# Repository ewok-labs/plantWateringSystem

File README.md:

plantWateringSystem
===================

plant watering system for the HPI HCI Lab, based on arduino

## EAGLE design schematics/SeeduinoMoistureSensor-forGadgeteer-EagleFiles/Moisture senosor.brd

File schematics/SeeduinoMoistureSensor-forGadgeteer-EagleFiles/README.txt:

Basically this is a gadgeteer compatible module (uses this 10-pin connector).
I've made it usable under arduino, the schematics from Seeduino guys are weird because they reported SIG_IN and SIG_OUT flipped (at least in my logic).
I've simple flipped them and renamed it to SIG_IN_REAL and SIG_OUT_REAL

The sensor will act like: http://www.seeedstudio.com/wiki/Grove_-_Moisture_Sensor
After you've connected the pins to the right place :) (and send a +5v on the SIG_INPUT_REAL)

It works.

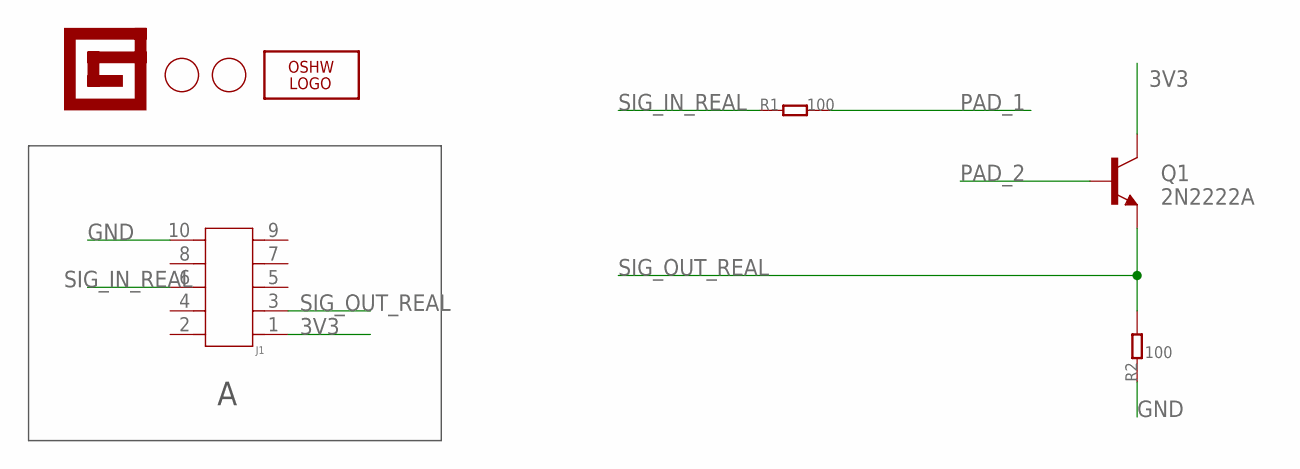
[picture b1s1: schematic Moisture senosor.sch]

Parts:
J1: HEADER-SHF-105-01-L-D-SM; SHF-105-01-L-D-SM
LOGO1: LOGO-OSHW-FILLX0150-NT; OSHW_FILLX150_NOTEXT
Q1: 2N2222A; TO-92
R1, R2: 100; 0603
U$1: LOGO-GADGETEER-NORMAL; GADGETEER-SILK
U$2, U$3: PAD-HOLE'3.2/7.0'; HOLE-D-3.2/7.0

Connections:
3V3: J1.1, Q1.3 (C)
GND: J1.10, R2.1
PAD_1: R1.2
PAD_2: Q1.2 (B)
SIG_IN_REAL: J1.6, R1.1
SIG_OUT_REAL: J1.3, Q1.1 (E), R2.2

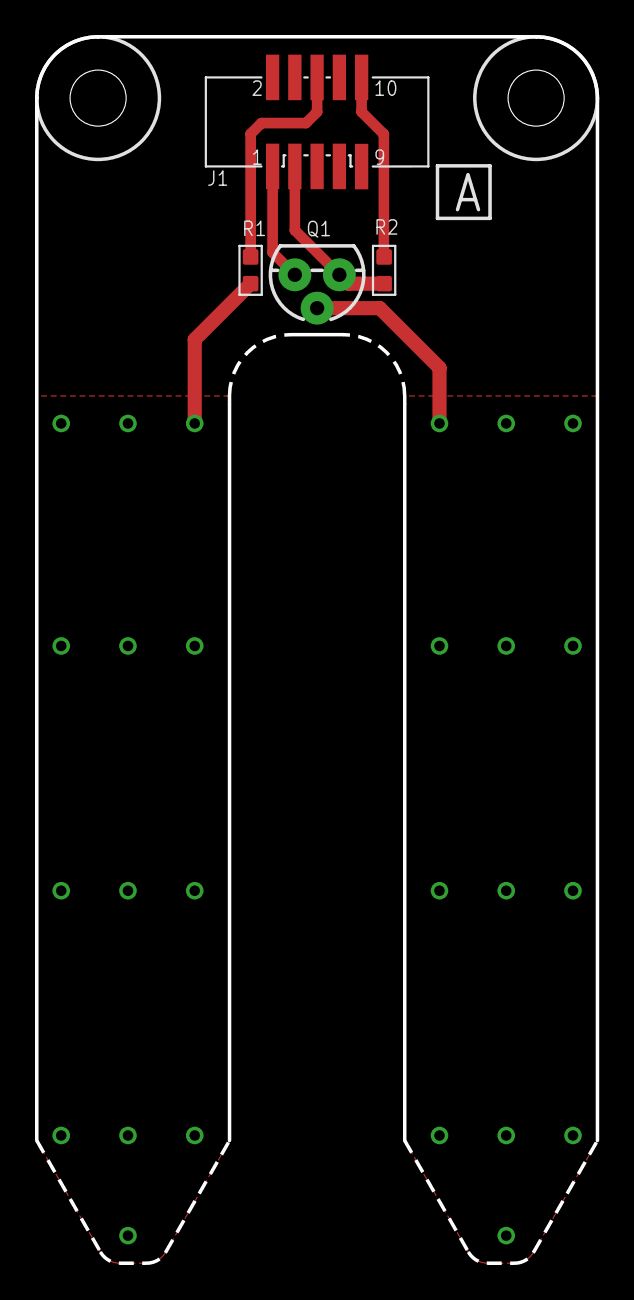
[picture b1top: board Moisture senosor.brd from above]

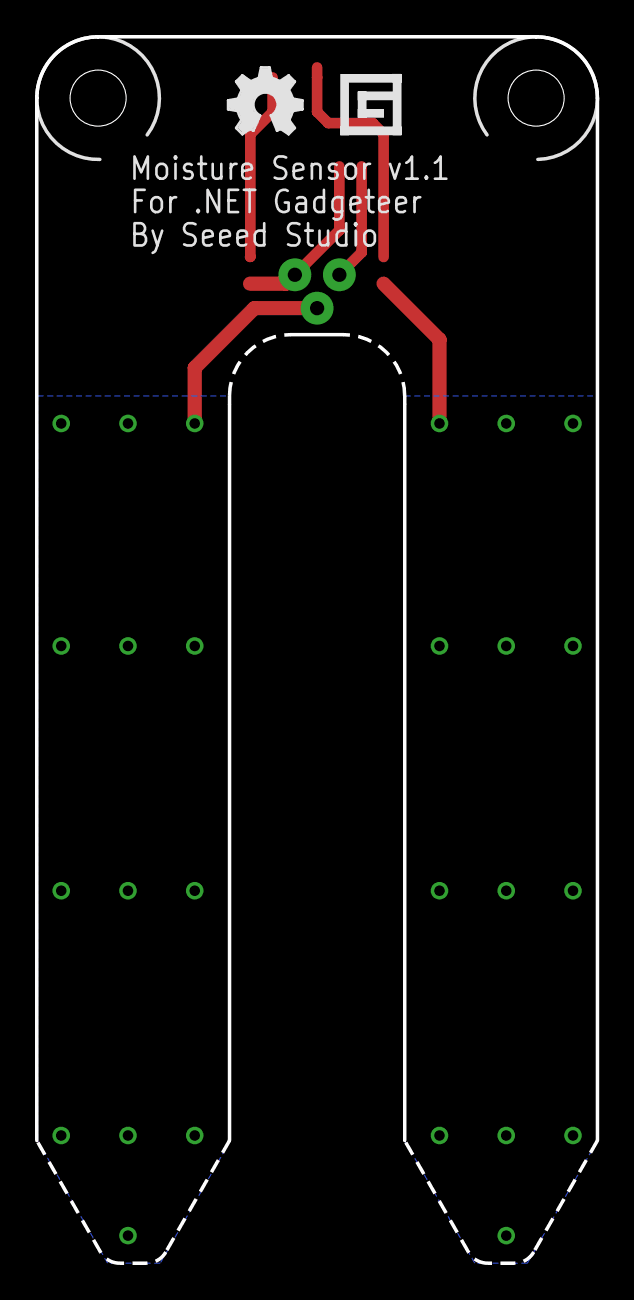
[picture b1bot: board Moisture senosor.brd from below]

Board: 2 copper layers, 32.0 x 70.0 mm, 8 parts (2 on the bottom side), 4 nets.

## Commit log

2014-07-17 schematics for gagdeteer to arduino sensor
2014-07-17 arduino code done on train
2014-07-17 modded gadgeteer sensor to arduino comments
2014-07-17 arduino code made on train had obvious weird bugs
2014-07-18 tested and works
2014-07-18 how to adapt gadgateer to arduino sensor, with photos
2014-07-18 eeprom code added, testing in progress.. takes time
2014-07-18 changed to support eeprom
2014-07-18 changed to support eeprom every 10 minutes, sweet
2014-08-21 adjustments before connects to the pc
